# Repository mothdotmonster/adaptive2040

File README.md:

# adaptive2040

Pi Pico expansion board for use with [GP2040-CE](https://gp2040-ce.info/)

Uses https://gitlab.com/recursivenomad/ki-lime-pi-pico

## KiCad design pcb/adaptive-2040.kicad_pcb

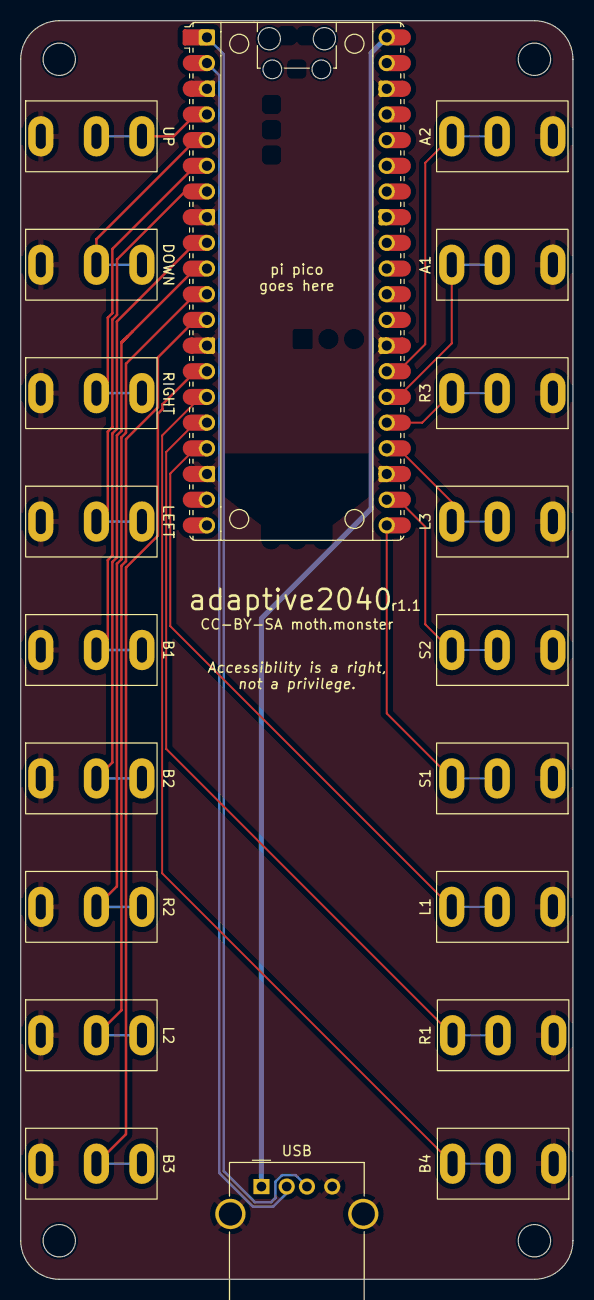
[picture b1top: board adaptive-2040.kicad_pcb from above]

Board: 2 copper layers, 54.6 x 124.5 mm, 24 parts (0 on the bottom side), 22 nets.

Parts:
J1: USB_A; USB_A_Molex_67643_Horizontal
J2, J3, J4, J5, J6, J7, J8, J9, J10, J11, J12, J13, J14, J15, J16, J17, J18, J19: AudioJack2; PJ-316
REF11, REF12, REF13, REF14145235: MountingHole_3.2mm_M3
U1: RaspberryPi_Pico; RaspberryPi_Pico_Common

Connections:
A1: J18.T, J18.TN, U1.26 (GPIO20)
A2: J19.T, J19.TN, U1.27 (GPIO21)
B1: J6.T, J6.TN, U1.9 (GPIO6)
B2: J7.T, J7.TN, U1.10 (GPIO7)
B3: J10.T, J10.TN, U1.14 (GPIO10)
B4: J11.T, J11.TN, U1.15 (GPIO11)
DM: J1.2 (D-), U1.2 (GPIO1)
DOWN: J3.T, J3.TN, U1.5 (GPIO3)
DP: J1.3 (D+), U1.1 (GPIO0)
GND: J1.4 (GND), J1.5 (Shield), J2.S, J3.S, J4.S, J5.S, J6.S, J7.S, J8.S, J9.S, J10.S, J11.S, J12.S, J13.S, J14.S, J15.S, J16.S, J17.S, J18.S, J19.S, U1.3 (GND), U1.8 (GND), U1.13 (GND), U1.18 (GND), U1.23 (GND), U1.28 (GND), U1.38 (GND)
L1: J13.T, J13.TN, U1.17 (GPIO13)
L2: J9.T, J9.TN, U1.12 (GPIO9)
L3: J16.T, J16.TN, U1.24 (GPIO18)
LEFT: J4.T, J4.TN, U1.6 (GPIO4)
R1: J12.T, J12.TN, U1.16 (GPIO12)
R2: J8.T, J8.TN, U1.11 (GPIO8)
R3: J17.T, J17.TN, U1.25 (GPIO19)
RIGHT: J5.T, J5.TN, U1.7 (GPIO5)
S1: J14.T, J14.TN, U1.21 (GPIO16)
S2: J15.T, J15.TN, U1.22 (GPIO17)
UP: J2.T, J2.TN, U1.4 (GPIO2)
VBUS: J1.1 (VBUS), U1.40 (VBUS)

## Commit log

2024-03-07 Rename adaptive-2040-nomoth.kicad_pcb to adaptive-2040.kicad_pcb
2024-03-07 reorganize
2024-03-07 license
2024-03-07 add schematic PDF
2024-03-07 tidy things up a little
2024-03-07 gerbers for convenience
2024-03-08 add render
2024-03-21 update gitignore
2024-03-21 r1 board
2024-03-21 update schematic and render
2024-03-21 update gerbers
2024-03-21 okay
2024-04-04 add enclosure
2024-04-04 fix case
2024-04-04 move schematic to pcb folder
2024-04-04 r1.1 - fix silkscreen error
2024-04-04 new render
2024-10-22 Update LICENSE

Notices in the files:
pcb/adaptive-2040.kicad_pcb:
CC-BY-SA moth.monster
